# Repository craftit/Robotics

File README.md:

# Robotics
This is a general scratch area for my robotics projects. One things are in decent shape I will organise and move them more appropriate.

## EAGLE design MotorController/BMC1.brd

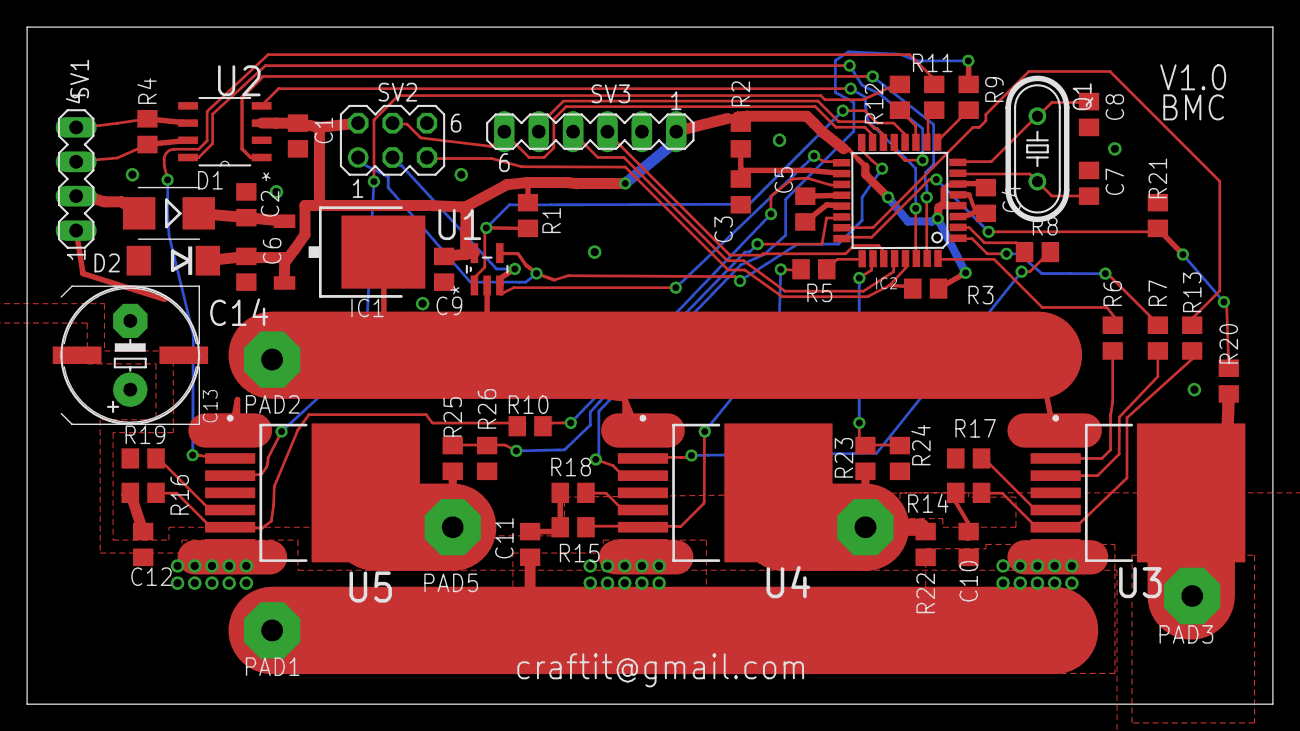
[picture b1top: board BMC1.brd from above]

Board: 2 copper layers, 92.0 x 50.0 mm, 58 parts (0 on the bottom side), 49 nets.

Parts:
C1, C3, C4, C5, C9: 0.1uf; C0805
C2: 10uf 35V; C0805
C6: 2.2uf 10V; C0805
C7, C8: 18pf; C0805
C10, C11, C12: 0.1uf 40v; C0805
C13: 1000uF 50V; UD-10X10_NICHICON
C14: 1000uf 50V; E5-10,5
D1: 50V; SMB
D2: 5.6V Zenner; DO214AA
IC1: LP2950; DPACK
IC2: MEGA8-AI; TQFP32-08
PAD1, PAD2, PAD3, PAD4, PAD5: WIREPAD4,16O1,6; 4,16O1,6
Q1: 20MHz; HC49/S
R1, R3, R5, R6, R7, R8, R9, R10, R11, R12, R13, R22: 10k; R0805
R2: 10uH; R0805
R4: 120R; R0805
R14, R15, R16: 750R; R0805
R17, R18, R19: 100R; R0805
R20, R23, R25: 30k; R0805
R21, R24, R26: 1k; R0805
SV1: MA04-1
SV2: MA03-2
SV3: MA06-1
U1: TC77-5.0MCTTR; SOT95P290X145-5N
U2: MCP2561-E/SN; SOIC127P600X175-8N
U3, U4, U5: BTN8982TA; TO127P1500X440-8N-1

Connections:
18V: C10.1, C11.1, C12.1, C13.+, C14.+, PAD1.1, R22.2, U3.7, U4.7, U5.7
+7V: D1.A, SV1.2
GND: C1.2, C2.2, C3.2, C4.2, C5.2, C6.2, C7.1, C8.1, C9.2, C10.2, C11.2, C12.2, C13.-, C14.-, D2.A, IC1.2, IC2.3, IC2.5, IC2.21, PAD2.1, R14.1, R15.1, R16.1, R17.1, R18.1, R19.1, R21.1, R24.1, R26.1, SV1.1, SV2.6, SV3.2, U1.2, U2.2, U3.1, U4.1, U5.1
unnamed: R17.2, U3.5
unnamed: PAD3.1, R20.2, U3.8
unnamed: R7.2, U3.3
unnamed: R6.2, U3.2
unnamed: IC2.24, R20.1, R21.2
unnamed: IC2.16, SV2.1, U1.4
unnamed: PAD4.1, R22.1, R23.2, U4.8
unnamed: R18.2, U4.5
unnamed: R9.2, U4.3
unnamed: R8.2, U4.2
unnamed: IC2.25, R5.1
unnamed: IC2.2, R8.1
unnamed: PAD5.1, R25.2, U5.8
unnamed: R19.2, U5.5
unnamed: R12.2, U5.3
unnamed: R11.2, U5.2
unnamed: IC2.19, R10.1
unnamed: IC2.22, R25.1, R26.2
unnamed: R4.1, SV1.4, U2.6
unnamed: IC2.9, R9.1
unnamed: IC2.26, R23.1, R24.2
unnamed: R4.2, SV1.3, U2.7
unnamed: IC2.13, U2.8
unnamed: C2.1, D1.C, IC1.1
unnamed: C7.2, IC2.7, Q1.2
unnamed: C8.2, IC2.8, Q1.1
unnamed: IC2.15, SV2.4, SV3.6
unnamed: IC2.32, R6.1
unnamed: IC2.17, SV2.3, U1.3
unnamed: R5.2, R15.2, U4.6
unnamed: IC2.27, SV3.3
unnamed: R13.2, R14.2, U3.6
unnamed: R10.2, R16.2, U5.6
unnamed: C3.1, IC2.18, R2.1
unnamed: IC2.28, SV3.4
unnamed: IC2.30, U2.4
unnamed: IC2.31, U2.1
unnamed: IC2.11, R12.1
unnamed: IC2.10, R11.1
unnamed: IC2.1, R7.1
unnamed: IC2.14, SV3.5
unnamed: IC2.12, R1.1, U1.1
unnamed: IC2.29, R3.2, SV2.5
unnamed: C5.1, IC2.20
unnamed: IC2.23, R13.1
VCC: C1.1, C4.1, C6.1, C9.1, D2.C, IC1.3, IC2.4, IC2.6, R1.2, R2.2, R3.1, SV2.2, SV3.1, U1.5, U2.3

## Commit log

2016-04-22 Add an initial version of the end plate.
2016-04-23 Add new parts.
2016-05-08 Add initial schematic for motor controller.
2016-05-14 Add a calibration object for hole sizes.
2016-05-30 Board layed out.
2016-05-30 Finished version 1.
2016-06-06 Updates.
2016-06-08 Add switching sequences.
2016-06-13 Added some interrupt handling.
2016-06-13 Set up of ADC.
2016-07-18 Stuff.
2016-07-19 More stl files.
2016-07-22 New parts.
2016-07-22 More updates.
2016-07-25 Fix constraints.
2016-07-25 Sort out files into the two different designs.
2016-07-29 New stl files.
2016-08-06 Initial end piece.
2016-08-06 New linear actuator.
2016-08-07 Add places for sensors.
2016-08-07 Make sensor holes smaller.
2016-08-13 Tweek sensor position
2016-08-13 Add stl files.
2016-09-08 Add parts for new gearbox.
2016-10-08 More parts.
2016-10-10 Starting to fit together.
2016-10-13 Add stl's of sun and planet gears.
2016-10-16 Motor turning.
2016-10-21 Using faster atan2 to avoid timing issues.
2016-10-23 Improved motor timing.
2016-10-23 More stuff.
2016-10-23 Add MT5208 motor mount.
2016-10-23 Add hip adaptor.
2016-10-25 Start work on new servo design.
2016-10-25 Base version of current servo.
2016-10-25 Some more current servo parts.
2016-10-25 New gearbox design.
2016-10-27 Working test bearing.
2016-10-28 Updated bearing to 40mm radius
2016-10-28 New carrier design.
2016-10-29 More fixes.
2016-10-30 Fixes for the carrier.
2016-11-02 Lots of fixes and updates.
2016-11-04 Start work on knee.
2016-11-08 Latest.
2016-11-12 Knee working.
2016-11-12 Added hip2.
2016-11-12 Fixed hip.
2016-11-13 Fix magnet removal slot.
2016-11-16 Wider hip joint.
2016-11-19 Fix push rod tails, and add notch to lower knee.
2016-11-22 Where we're at.
2016-11-22 Clean up.
2016-12-24 Work on new motor controller.
2016-12-31 Most of new motor controller schematic, and leg V2.
2017-01-04 Initial schematic complete.
2017-01-04 Component footprints.
2017-01-05 Design tweeks.
2017-01-05 Add local library.
2017-01-05 Work on PCB layout.
2017-01-10 Laying out power section.
2017-01-13 More of the layout done.
2017-01-13 More tweaks
2017-01-15 Layout nearly complete.
2017-01-15 Tweaks.
2017-01-16 Put in Champers for screws.
2017-01-16 About to change via drill size.
2017-01-16 Nearly there.
2017-01-16 Fixes for soldermask clearences
2017-01-22 Make tool hole a little bigger.
2017-01-22 Remove obsolete parts.
2017-01-22 Add 3 hall sensor mount.
2017-01-23 Add pelvis and refine motor mount.
2017-01-24 Add TODO list.
2017-01-25 Add body brackets.
2017-01-26 Add bumper to body bracket.
2017-01-27 Work on BOM.
2017-01-27 Add some vias
2017-01-28 Fix UpperKnee race.
2017-02-02 Tweaks to PCB.
2017-02-02 Make holes more recessed.
2017-02-12 Started on firmware.
2017-02-15 We have a USB device.
2017-02-16 Have a terminal up and running as well as adc.
2017-02-20 Some progress.
2017-02-20 More testing.
2017-02-27 A bit more work on wire wiggling.
2017-03-04 Move firmware into its own repo.
2017-05-08 Add new hip reinforcement with holes for the motor controller mount.
2017-05-15 Update end stop to be a ring.
2017-09-21 BMCV2.1 updates.
2017-09-22 Add power off option.
2017-09-22 Start on sensor board layout.
2017-09-22 Start on board outline.
2017-09-22 Final board.
2017-09-22 Board layouts as ordered.
2017-11-01 Updates for parts list.
2017-11-01 Update part number.
2017-11-29 Add index sensor plug.
2017-12-07 Add some annotations.
